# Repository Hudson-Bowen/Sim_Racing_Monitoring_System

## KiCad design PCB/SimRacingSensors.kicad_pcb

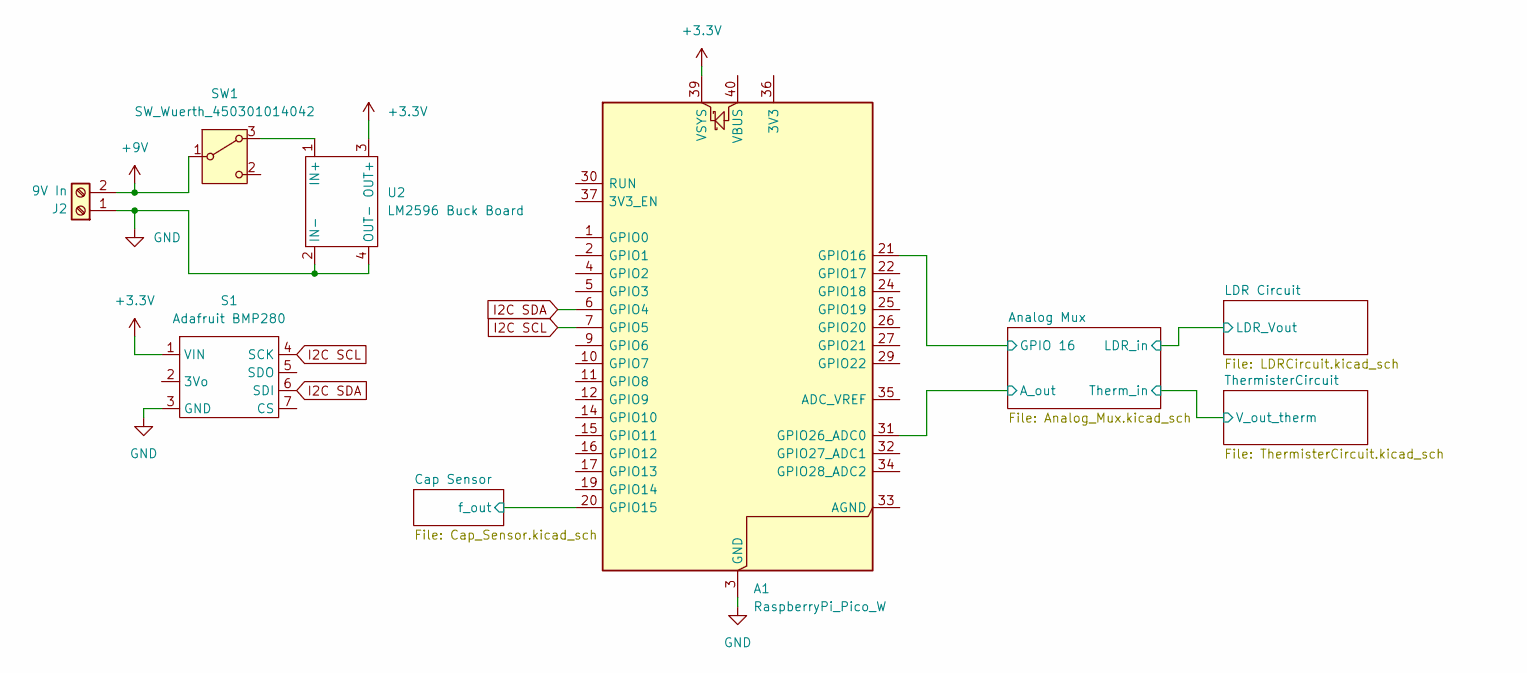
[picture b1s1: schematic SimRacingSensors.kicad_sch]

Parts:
A1: RaspberryPi_Pico_W; RaspberryPi_Pico_W_SMD_HandSolder
J2: 9V In; TerminalBlock_Phoenix_MKDS-1,5-2-5.08_1x02_P5.08mm_Horizont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
S1: Adafruit BMP280
SW1: SW_Wuerth_450301014042; SW_Slide-03_Wuerth-WS-SLTV_10x2.5x6.4_P2.54mm
U2: LM2596 Buck Board; LM2596 Buck Converter Footprint

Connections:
+3.3V: A1.39 (VSYS), S1.1 (VIN), U2.3 (OUT+); also elsewhere on the board
/Analog Mux/A_out: A1.31 (GPIO26_ADC0); also elsewhere on the board
/Analog Mux/GPIO 16: A1.21 (GPIO16); also elsewhere on the board
/Cap Sensor/f_out: A1.20 (GPIO15); also elsewhere on the board
GND: A1.3 (GND), A1.8 (GND), A1.13 (GND), A1.18 (GND), A1.23 (GND), A1.28 (GND), A1.38 (GND), J2.1, S1.3 (GND), U2.2 (IN-), U2.4 (OUT-); also elsewhere on the board
I2C SCL: A1.7 (GPIO5), S1.4 (SCK)
I2C SDA: A1.6 (GPIO4), S1.6 (SDI)
unnamed: J2.2, SW1.1 (B)
unnamed 24: SW1.3 (A), U2.1 (IN+); also elsewhere on the board

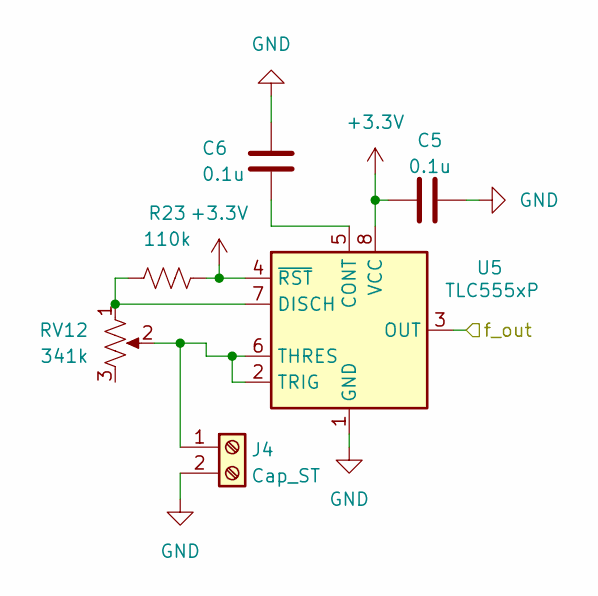
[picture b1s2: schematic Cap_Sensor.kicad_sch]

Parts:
C5, C6: 0.1u; C_Disc_D5.0mm_W2.5mm_P5.00mm
J4: Cap_ST; TerminalBlock_Phoenix_MKDS-1,5-2-5.08_1x02_P5.08mm_Horizont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
R23: 110k; R_Axial_DIN0207_L6.3mm_D2.5mm_P10.16mm_Horizontal
RV12: 341k; Rotary Pot Kit Footprint
U5: TLC555xP; DIP-8_W7.62mm

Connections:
+3.3V: C5.1, R23.2, U5.4 (~RST), U5.8 (VCC); also elsewhere on the board
/Cap Sensor/f_out: U5.3 (OUT); also elsewhere on the board
GND: C5.2, C6.2, J4.2, U5.1 (GND); also elsewhere on the board
unnamed 14: J4.1, RV12.2, U5.2 (TRIG), U5.6 (THRES); also elsewhere on the board
unnamed: C6.1, U5.5 (CONT)
unnamed: R23.1, RV12.1, U5.7 (DISCH)

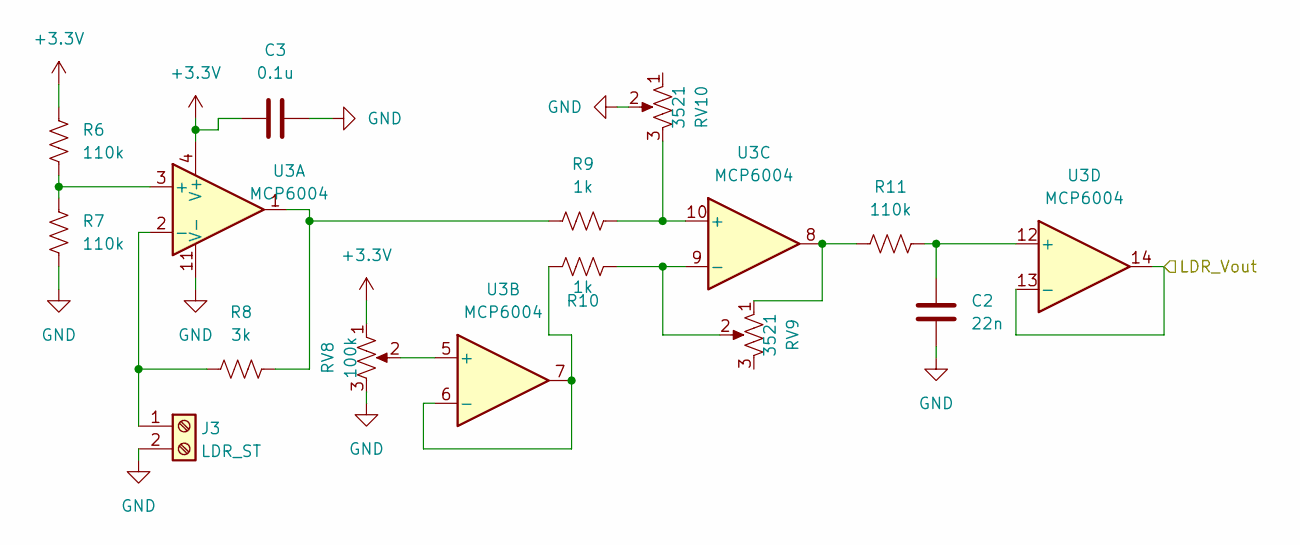
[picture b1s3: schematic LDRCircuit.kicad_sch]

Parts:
C2: 22n; C_Disc_D5.0mm_W2.5mm_P5.00mm
C3: 0.1u; C_Disc_D5.0mm_W2.5mm_P5.00mm
J3: LDR_ST; TerminalBlock_Phoenix_MKDS-1,5-2-5.08_1x02_P5.08mm_Horizont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
R6, R7, R11: 110k; R_Axial_DIN0207_L6.3mm_D2.5mm_P10.16mm_Horizontal
R8: 3k; R_Axial_DIN0207_L6.3mm_D2.5mm_P10.16mm_Horizontal
R9, R10: 1k; R_Axial_DIN0207_L6.3mm_D2.5mm_P10.16mm_Horizontal
RV8: 100k; Potentiometer_Bourns_3386F_Vertical
RV9, RV10: 3521; Potentiometer_Bourns_3386H_Horizontal
U3: MCP6004; DIP-14_W7.62mm_LongPads

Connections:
+3.3V: C3.1, R6.1, RV8.1, U3.4 (V+); also elsewhere on the board
/Analog Mux/LDR_in: U3.13 (-), U3.14; also elsewhere on the board
GND: C2.2, C3.2, J3.2, R7.2, RV8.3, RV10.2, U3.11 (V-); also elsewhere on the board
unnamed 13: J3.1, R8.1, U3.2 (-); also elsewhere on the board
unnamed: R8.2, R9.1, U3.1
unnamed: R11.1, RV9.1, U3.8
unnamed: R6.2, R7.1, U3.3 (+)
unnamed: RV8.2, U3.5 (+)
unnamed: R10.1, U3.6 (-), U3.7
unnamed: R9.2, RV10.3, U3.10 (+)
unnamed: R10.2, RV9.2, U3.9 (-)
unnamed: C2.1, R11.2, U3.12 (+)

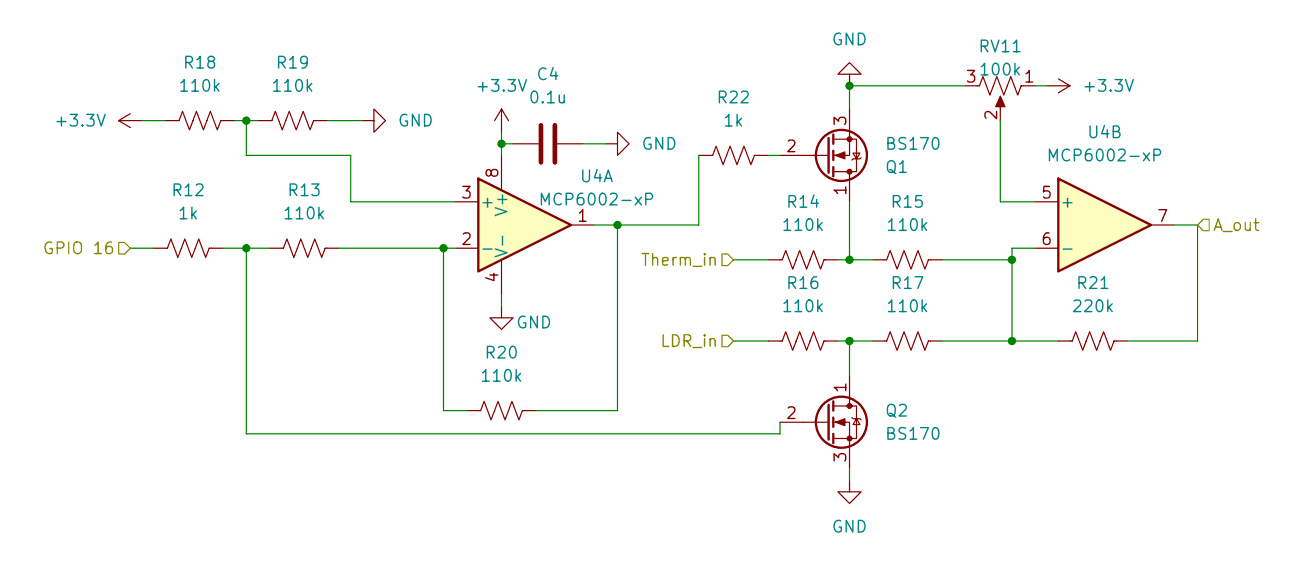
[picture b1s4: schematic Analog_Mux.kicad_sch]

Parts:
C4: 0.1u; C_Disc_D5.0mm_W2.5mm_P5.00mm
Q1, Q2: BS170; TO-92_Inline
R12, R22: 1k; R_Axial_DIN0207_L6.3mm_D2.5mm_P10.16mm_Horizontal
R13, R14, R15, R16, R17, R18, R19, R20: 110k; R_Axial_DIN0207_L6.3mm_D2.5mm_P10.16mm_Horizontal
R21: 220k; R_Axial_DIN0207_L6.3mm_D2.5mm_P10.16mm_Horizontal
RV11: 100k; Potentiometer_Bourns_3386F_Vertical
U4: MCP6002-xP; DIP-8_W7.62mm_LongPads

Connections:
+3.3V: C4.1, R18.1, RV11.1, U4.8 (V+); also elsewhere on the board
/Analog Mux/A_out: R21.2, U4.7; also elsewhere on the board
/Analog Mux/GPIO 16: R12.1; also elsewhere on the board
/Analog Mux/LDR_in: R16.1; also elsewhere on the board
/Analog Mux/Therm_in: R14.1; also elsewhere on the board
GND: C4.2, Q1.3 (S), Q2.3 (S), R19.2, RV11.3, U4.4 (V-); also elsewhere on the board
unnamed: Q1.1 (D), R14.2, R15.1
unnamed: Q1.2 (G), R22.2
unnamed: Q2.1 (D), R16.2, R17.1
unnamed: Q2.2 (G), R12.2, R13.1
unnamed: R20.2, R22.1, U4.1
unnamed: R18.2, R19.1, U4.3 (+)
unnamed: R13.2, R20.1, U4.2 (-)
unnamed: RV11.2, U4.5 (+)
unnamed: R15.2, R17.2, R21.1, U4.6 (-)

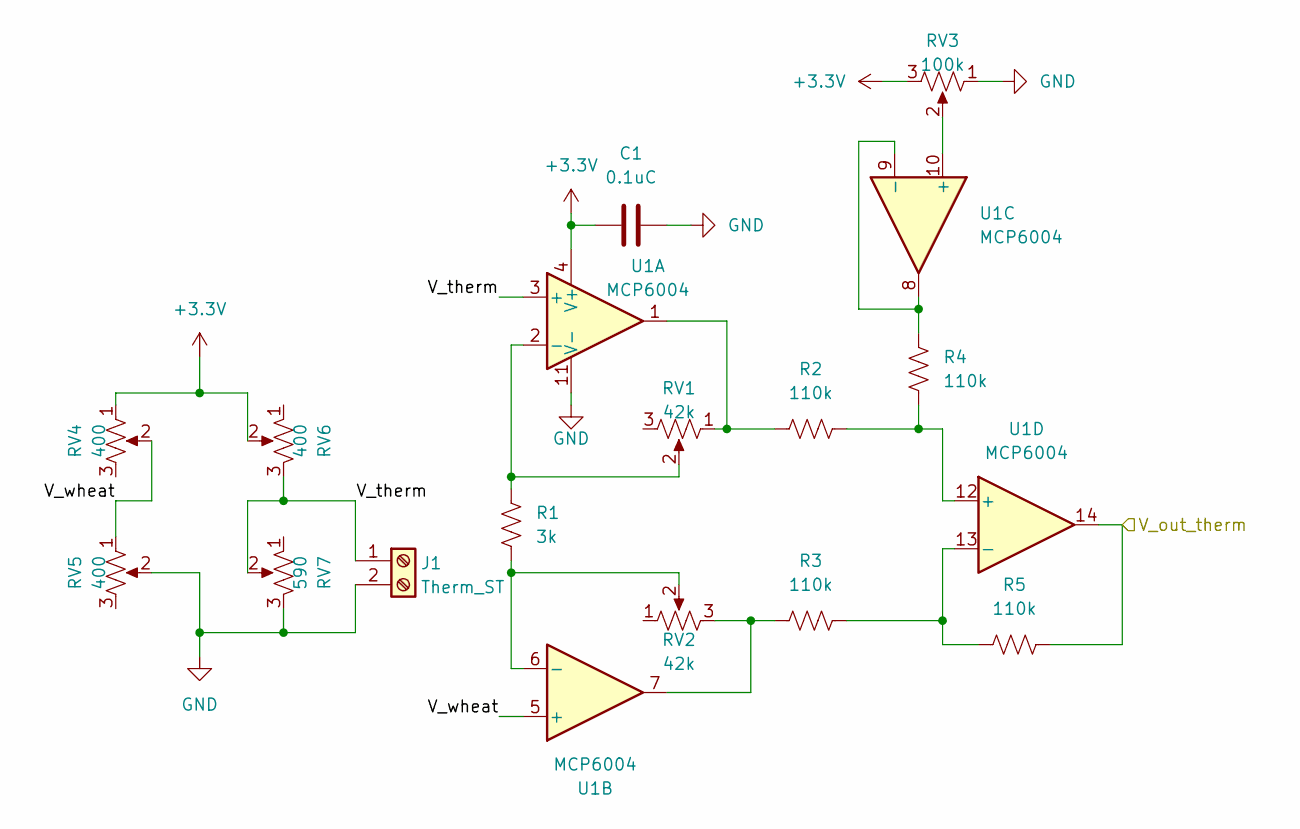
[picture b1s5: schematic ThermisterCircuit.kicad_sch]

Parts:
C1: 0.1uC; C_Disc_D5.0mm_W2.5mm_P5.00mm
J1: Therm_ST; TerminalBlock_Phoenix_MKDS-1,5-2-5.08_1x02_P5.08mm_Horizont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
R1: 3k; R_Axial_DIN0207_L6.3mm_D2.5mm_P10.16mm_Horizontal
R2, R3, R4, R5: 110k; R_Axial_DIN0207_L6.3mm_D2.5mm_P10.16mm_Horizontal
RV1, RV2: 42k; Potentiometer_Bourns_3386F_Vertical
RV3: 100k; Potentiometer_Bourns_3386F_Vertical
RV4, RV5, RV6: 400; Potentiometer_Bourns_3386H_Horizontal
RV7: 590; Potentiometer_Bourns_3386H_Horizontal
U1: MCP6004; DIP-14_W7.62mm_LongPads

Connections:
+3.3V: C1.1, RV3.3, RV4.1, RV6.2, U1.4 (V+); also elsewhere on the board
/Analog Mux/Therm_in: R5.2, U1.14; also elsewhere on the board
/ThermisterCircuit/V_therm: J1.1, RV6.3, RV7.2, U1.3 (+); also elsewhere on the board
/ThermisterCircuit/V_wheat: RV4.2, RV5.1, U1.5 (+)
GND: C1.2, J1.2, RV3.1, RV5.2, RV7.3, U1.11 (V-); also elsewhere on the board
unnamed: R2.1, RV1.1, U1.1
unnamed: R3.1, RV2.3, U1.7
unnamed: R1.1, RV1.2, U1.2 (-)
unnamed: R1.2, RV2.2, U1.6 (-)
unnamed: RV3.2, U1.10 (+)
unnamed: R4.2, U1.8, U1.9 (-)
unnamed: R2.2, R4.1, U1.12 (+)
unnamed: R3.2, R5.1, U1.13 (-)

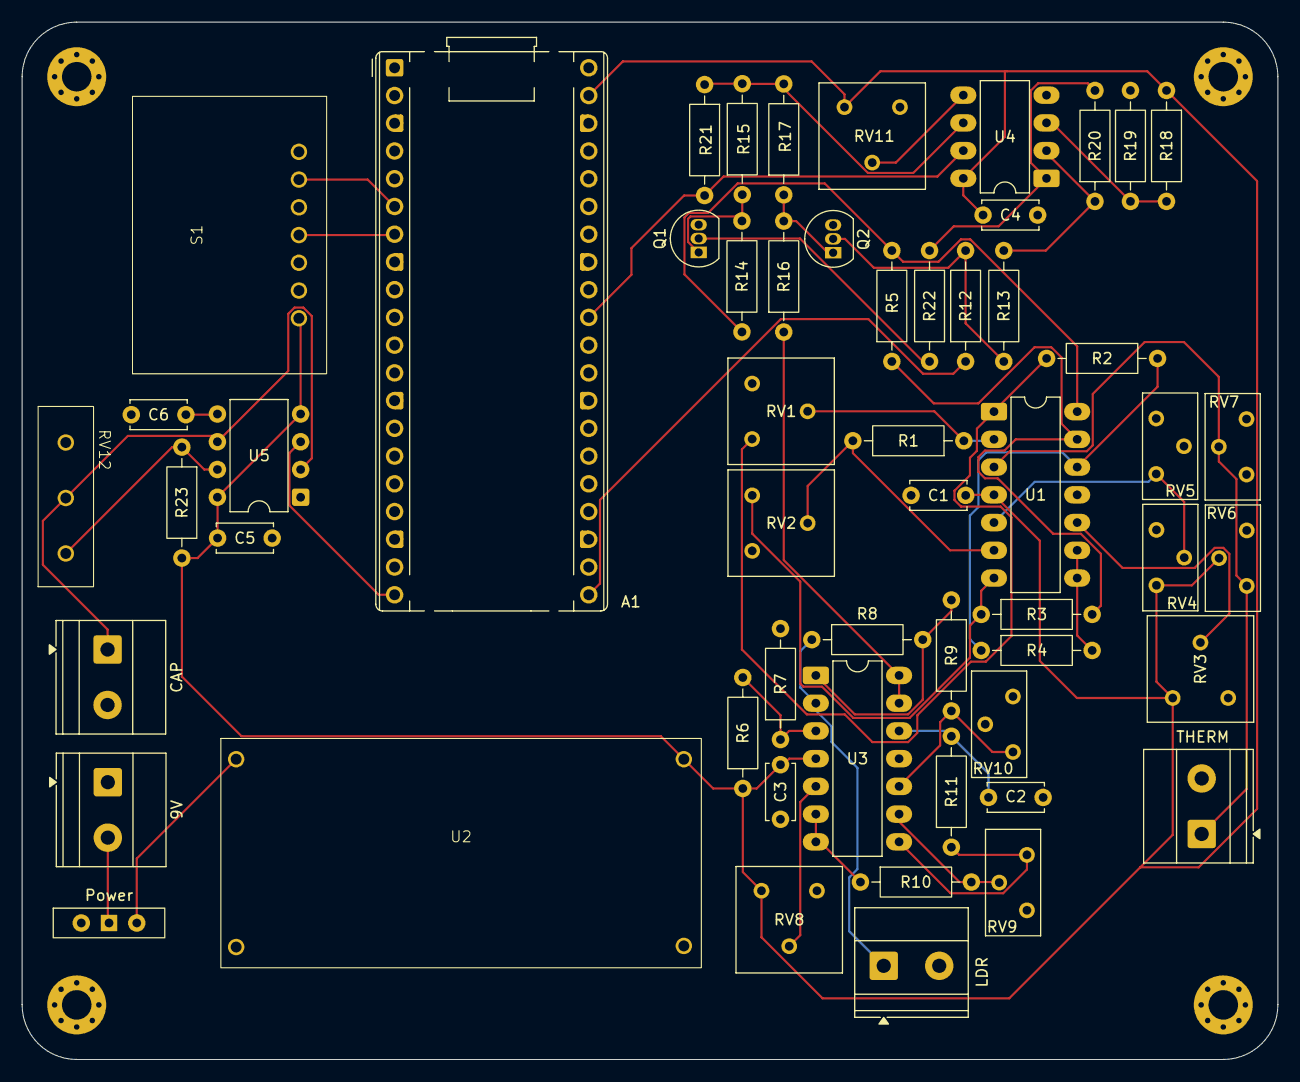
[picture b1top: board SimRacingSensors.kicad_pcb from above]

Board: 2 copper layers, 115.0 x 95.0 mm, 55 parts (0 on the bottom side), 42 nets.

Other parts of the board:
9V: 9V In; TerminalBlock_Phoenix_MKDS-1,5-2-5.08_1x02_P5.08mm_Horizont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
CAP: Cap_ST; TerminalBlock_Phoenix_MKDS-1,5-2-5.08_1x02_P5.08mm_Horizont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
LDR: LDR_ST; TerminalBlock_Phoenix_MKDS-1,5-2-5.08_1x02_P5.08mm_Horizont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
Power: SW_Wuerth_450301014042; SW_Slide-03_Wuerth-WS-SLTV_10x2.5x6.4_P2.54mm
THERM: Therm_ST; TerminalBlock_Phoenix_MKDS-1,5-2-5.08_1x02_P5.08mm_Horizont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

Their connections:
+9V: 9V.2, Power.1 (B)
/ThermisterCircuit/V_therm: THERM.1; also elsewhere on the board
GND: 9V.1, CAP.2, LDR.2, THERM.2; also elsewhere on the board
unnamed 13: LDR.1; also elsewhere on the board
unnamed 14: CAP.1; also elsewhere on the board
unnamed 24: Power.3 (A); also elsewhere on the board
